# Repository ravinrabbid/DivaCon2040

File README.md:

# DivaCon2040 - Firmware for RP2040/RP2350 based Project Diva controllers

DivaCon2040 is a firmware for DIY Project Diva Arcade controllers based on the RP2040/RP2350 microcontroller as found on the Raspberry Pi Pico.

It is pretty much tailored to this specific use case, if you are looking for something universal, ready-to-flash and on-the-fly configurable I'd recommend to have a look at more generic approaches like [GP2040-CE](https://github.com/OpenStickCommunity/GP2040-CE). If you however want build something more specialized or custom, feel free to use this project as a base, it is designed to be somewhat modular and should be easy remodel. See [DonCon2040](https://github.com/ravinrabbid/DonCon2040) for an example on how this could look like.

If you have any questions about the project in general or need hints how to build this thing, feel free to open a [discussion](https://github.com/ravinrabbid/DivaCon2040/discussions) anytime!

## Features

- Various controller emulation modes
  - HORI PS4-161 Project Diva Arcade Controller
  - HORI NSW-230 Project Diva Arcade Controller
  - PD-Loader Arcade Controller (Compatible with [PD-Loader](https://github.com/PDModdingCommunity/PD-Loader/)'s Divaller driver)
  - PS4 Compatibility (will work on PS4, see [PS4 Authentication](#ps4-authentication) for details)
  - Dualshock 4 (Will be recognised as DS4 on PC/Steam, but does not work on an actual PS4!)
  - Dualshock 3
  - Switch Pro Controller
  - XInput
  - Keyboard
  - MIDI
  - Debug mode (will output current state via USB serial and allow direct flashing)
- Arcade Style Touch Slider for arcade controller emulation modes (In Project Diva Games with arcade controller support: Enter the 'Customize' menu from song selection and enable arcade controller support under 'Game/Control Config' -> 'Arcade Controller Settings' for the slider to work properly.)
- Slider to analog stick mapping for standard controller modes
- Option to mirror face buttons to directional pad for games with 'W'-arrows
- 1000Hz Polling Rate, ~2.4ms average latency, <0.7ms Jitter (Tested with [Gamepadla](https://github.com/cakama3a/Gamepadla)/[GPDL](https://github.com/cakama3a/GPDL/))
- Slider illumination using WS2812 LED strip (can be controlled by PD-Loader)
- Button illumination (can be controlled by PD-Loader)
- Basic configuration via on-screen menu on attached OLED screen
- BPM counter

## Game Compatibility

| Title                                                                       | Platform | Official Arcade Slider Support |      Recommended Mode      | Notes                                                                                                                                                                                                                                                                                                                                                |
| --------------------------------------------------------------------------- | :------: | :----------------------------: | :------------------------: | :--------------------------------------------------------------------------------------------------------------------------------------------------------------------------------------------------------------------------------------------------------------------------------------------------------------------------------------------------- |
| Hatsune Miku -Project DIVA- Dreamy Theater                                  |   PS3    |               No               | Dualshock 3 + 'Double Btn' | - **Untested** but will likely work.<br>- Slider can be used for Star notes.<br>- Enable 'Double Btn' to make hitting 'W'-arrows easier.                                                                                                                                                                                                             |
| Hatsune Miku -Project DIVA- Dreamy Theater 2nd                              |   PS3    |               No               | Dualshock 3 + 'Double Btn' | - Slider can be used for Star notes.<br>- Enable 'Double Btn' to make hitting 'W'-arrows easier.                                                                                                                                                                                                                                                     |
| Hatsune Miku -Project DIVA- Dreamy Theater extend                           |   PS3    |               No               | Dualshock 3 + 'Double Btn' | - **Untested** but will likely work.<br>- Slider can be used for Star notes.<br>- Enable 'Double Btn' to make hitting 'W'-arrows easier.                                                                                                                                                                                                             |
| Hatsune Miku -Project DIVA- F                                               |   PS3    |               No               | Dualshock 3 + 'Double Btn' | - Slider can be used for Star notes.<br>- Enable 'Double Btn' to make hitting 'W'-arrows easier.                                                                                                                                                                                                                                                     |
| Hatsune Miku -Project DIVA- F2nd                                            |   PS3    |               No               | Dualshock 3 + 'Double Btn' | - Slider can be used for Star notes.<br>- Enable 'Double Btn' to make hitting 'W'-arrows easier.                                                                                                                                                                                                                                                     |
| Hatsune Miku -Project DIVA- Future Tone                                     |   PS4    |               No               |         PS4 Compat         | - See [PS4 Authentication](#ps4-authentication)<br>- Game does not support arcade style slider, stick emulation will be used.                                                                                                                                                                                                                        |
| Hatsune Miku -Project DIVA- Future Tone DX                                  |   PS4    |              Yes               |          PS4 Diva          | - See [PS4 Authentication](#ps4-authentication)<br>- From song selection enter the 'Customize' menu and enable arcade controller support under 'Game/Control Config' -> 'Arcade Controller Settings'.                                                                                                                                                |
| Hatsune Miku -Project DIVA- X                                               |   PS4    |               No               | PS4 Compat + 'Double Btn'  | - See [PS4 Authentication](#ps4-authentication)<br>- Slider can be used for Star notes.<br>- Enable 'Double Btn' to make hitting 'W'-arrows easier.                                                                                                                                                                                                  |
| Hatsune Miku: Project DIVA Mega Mix / Hatsune Miku -Project DIVA- MEGA39’s  |  Switch  |              Yes               |        Switch Diva         | - When starting the game, choose 'Arcade Mode'.<br> - From song selection enter the 'Customize' menu and enable arcade controller support under 'Game/Control Config' -> 'Arcade Controller Settings'.                                                                                                                                               |
| Hatsune Miku -Project DIVA- Arcade Future Tone (PDLoader)                   |    PC    |              Yes               |         PDL Arcade         | - Should work out-of-the-box. (You might need to enable `slider_in_menus` in `keyconfig.ini` and `Hardware_Slider` in `config.ini`).<br>- 'PS4 Diva' also works, see [here](https://github.com/PDModdingCommunity/PD-Loader/wiki/3%29-Usage,-Modules-%28Costumes%29,-Troubleshooting#official-hori-ps4-ft-controller-with-slider) for configuration. |
| Hatsune Miku: Project DIVA Mega 39s+ / Hatsune Miku: Project DIVA Mega Mix+ |    PC    |              Yes               |  PS4 Diva or Switch Diva   | - From song selection enter the 'Customize' menu and enable arcade controller support under 'Game/Control Config' -> 'Arcade Controller Settings'.                                                                                                                                                                                                   |

## Building

I highly recommend to build the firmware yourself so you can make adjustments in `include/GlobalConfiguration.h` to match your specific controller build.
If you still want to use a [binary release](https://github.com/ravinrabbid/DivaCon2040/releases), you need to connect everything according the default configuration as described [here](SCHEMATIC.md).

### VSCode (Windows, Linux, MacOS)

Install [VSCode](https://code.visualstudio.com/) and get the [Raspberry Pi Pico](https://marketplace.visualstudio.com/items?itemName=raspberry-pi.raspberry-pi-pico) extension. From the extension choose 'Import Project' and select the folder where you've checked out this repository, then use 'Compile Project'.

### CLI

See [pico-sdk readme](https://github.com/raspberrypi/pico-sdk/blob/master/README.md#quick-start-your-own-project) for a list of pre-requisites.

Use the environment variables `PICO_SDK_PATH` to use a local pico-sdk, and `PICO_BOARD` to select another target board.
By default the pico-sdk will be fetched from Github and the target board will be "pico".

For Rasberry Pi Pico:

```sh
cmake -B build -DPICO_BOARD="pico"
cmake --build build
```

For Rasberry Pi Pico 2:

```sh
cmake -B build -DPICO_BOARD="pico2"
cmake --build build
```

## Configuration

Options which you probably want to change more regularly can be changed using the on-screen menu on the attached OLED display, hold both Start and Select for 2 seconds to enter it:

- Controller emulation mode
- Touch Slider LED mode, color and brightness
- Face button to directional pad mirroring
- Reset settings to defaults
- Enter BOOTSEL mode for firmware flashing

Those settings are persisted to flash memory if you choose 'Save' when exiting the Menu and will survive power cycles.

Everything else is compiled statically into the firmware. You can find defaults and hardware configuration in `include/GlobalConfiguration.h`. This covers default controller emulation mode, button pins, i2c pins, addresses and speed and slider type.

### PS4 Authentication

The PS4 needs a controller to sign a cryptographic challenge every few seconds, otherwise it will stop working after around 8 minutes after plugging in. For the Project Diva games this is somewhat bearable, since you can re-plug the controller before starting each song to avoid running into the timeout during gameplay. Still, this is annoying.

DivaCon2040 can sign those challenges, but you will need to obtain some data from an original DS4 and compile it into the firmware. You will need a serial, signature and private key file. I can't and won't help you how to obtain those, you'll need to figure this out yourself.

To build the firmware run `scripts/generateAuthConfig.py` in the folder where you placed the required files. Copy the resulting `PS4AuthConfiguration.h` to the `include` directory, replacing the existing header. Then build the firmware as described in [Building](#building).

Signing the challenge will block the second core of the RP2040 for 2-3 seconds, so LED animations and the display will appear stuck from time to time. Input handling is unaffected.
On the RP2350 SHA256 is hardware accelerated, so signing time is reduced to about 1 second.

## Hardware

### Main IO Board

This project was designed and tested on the Raspberry Pi Pico. Other RP2040/RP2350 boards should also work if they expose enough GPIOs.

You can find the [DivaConIO board](pcb/DivaConIO) in the *pcb* subfolder. This conveniently breaks out the GPIO pins into connectors and already comes with drivers for the button LEDs and level shifting for the slider LEDs.

It is however perfectly possible to build this on a piece of stripboard or the like. [See this schematic here](SCHEMATIC.md) for details.

### Touch Slider

The touch slider resembles the the slider of Project Diva Arcade Controllers and Cabinets, being a row of 32 individual touch sensors. For the two arcade controller emulation modes, the 32 sensors are mapped to the analog stick axes as described [here](https://gist.github.com/dogtopus/48ad10409aa4ad5c408e31287623e167) and work just like the original controllers in-game. In Project Diva games which support arcade controllers (i.e. Mega Mix on PC/Switch), enter the 'Customize' menu from song selection and enable arcade controller support under 'Game/Control Config' -> 'Arcade Controller Settings' for the slider to work properly.

For other controller emulation modes, swipes on the left half of the slider will move the left stick left and right, while swipes on the right half will do the same on the right stick.

#### Electronics

The current Touch Slider is based on the MPR121 Capacitive Touch Sensor Controller. While the MPR121 seems to have a somewhat bad reputation to be hard to work with, I've had no issues with it so far and it works near flawlessly. That main downside is that is is out-of-production, there is however still sufficient supply on the usual marketplaces.

Current alternatives like the CAP1188 are almost universally to slow. During a quick slide, a finger spends roughly 10ms on a single touch pad while most controllers need scan cycles of at least 16-35ms. The MPR121 on the contrary can be configured down to around 1ms. The Lumissil IS31SE5117A looks promising, but I couldn't get it to work yet. Other than that microcontrollers with integrated touch controllers are an option, but I don't want to go down that route since there already is the [LKP](https://github.com/Project-Alpaca/LKP) which does this. The LKP seems to have an i2c slave mode, so if you have access to one feel free to get in touch. I'd be happy to work on supporting the LKP but need someone to test.

All MPR121 controllers are attached to the same i2c bus, so make sure to have them use different i2c addresses accordingly. There is a slider variant with three and one with four controllers which can be configured in `include/GlobalConfiguration.h` (The four controller variant is the default). See below tables for the electrode mapping:

##### Three MPR121

|               | **MPR 0** | **MPR 1** | **MPR 2** |
| ------------- | :-------: | :-------: | :-------: |
| **Pin**       |   0..11   |   2..9    |   0..11   |
| **Electrode** |  31..20   |  19..12   |   11..0   |

##### Four MPR121

|               | **MPR 0** | **MPR 1** | **MPR 2** | **MPR 3** |
| ------------- | :-------: | :-------: | :-------: | :-------: |
| **Pin**       |   4..11   |   4..11   |   4..11   |   4..11   |
| **Electrode** |  31..24   |  13..16   |   15..8   |   7..0    |

The MPR121s are setup for auto configuration with parameters taken from the [Adafruit MPR121 Arduino Library](https://github.com/adafruit/Adafruit_MPR121). The 'FDL falling' value has been tweaked to allow slow slides. You might want to adjust the touch and release thresholds to your specific build.

#### Construction

There are two variants which both work equivalently well in my experience: You can use the [DivaConSlider board](pcb/DivaConSliderMpr) from the *pcb* subfolder which hosts the MPR121s, electrodes and LEDs or you can build it by hand without a pcb.

For the latter I had success using 15mm wide copper tape strips with 2mm spacing in-between, aligning them properly using a 3D printed jig. Those are attached to off-the-shelf MPR121 breakout boards using the thinnest wire possible to reduce parasitic capacitance.

Both variants are covered by a sandwich made out of some thin 3M 468MP or 467MP adhesive, paper for the artwork, another layer of adhesive and 3mm of frosted acrylic. Is seems to be pretty essential to use the proper adhesive here to get an even bond and to avoid any air between the layers. The 3M tape mentioned above is recommended in the MPR121 application notes. I can be a bit hard to work with, but is manageable by spraying some soapy water on the surface beforehand to ease alignment.

For illumination of the non-pcb variant, I used [Adafruit Side Light NeoPixel LED PCB Bars](https://www.adafruit.com/product/3729) which have the perfect hight and spacing to light up each segment with two LEDs each, but other WS2812 compatible strips should work as well.

One word on the slider dimensions: Those are not arcade accurate but slightly larger. This stems from constraints of me building the non-pcb variant first (i.e. available copper tape and LED strip dimensions). See [here](https://projectdiva.net/community/threads/i-bought-a-project-diva-arcade-future-tone-cabinet.2307/page-3#post-18087) for the actual dimensions or have a look at the [LKP](https://github.com/Project-Alpaca/LKP).

### Buttons

Buttons are hooked up directly to the GPIO pins, pulling the pin to ground when pressed.

Supported are:

- Four face buttons, which are mapped according to the cardinal directions they appear on the respective controllers (North/East/South/West)
- DPad/Hat (Up/Down/Left/Right)
- Two shoulder buttons for each side (L1/L2/R1/R2)
- Two Stick buttons (L3/R3)
- Three vendor specific buttons (Options/TouchPad/PS on DS4, Start/Select/PS on DS3, +/-/Home on Switch, Start/Back/Guide on XInput)

For the four big buttons I used generic 100mm "Massive Arcade Button"s since those are much cheaper than the original Sanwa OBSA-100UMQ.
They have same size an can be easily improved with the original OBSA-SP-200 200g springs and better switches, like the ridiculously expensive Sanwa OBSA-LHSXF or [steelpuxnastik's excellent DIY switches](https://github.com/steelpuxnastik/SHINSANWASWITCH) for a more authentic feel.

The other buttons are cheap generic 24mm arcade buttons.

### Button LEDs

Illumination for the four face buttons can be controlled by GPIO pins. I recommend to not directly hook up the LEDs to the GPIO pins, but rather use a simple transistor based driving circuit since the power than can be delivered through the GPIOs is rather limited.

### OLED Display

Just a standard SSD1306 OLED display with 128x64 resolution hooked up to the second i2c bus. Mind that the display is mandatory for changing any settings directly on the controller, if you want to omit it, change the defaults within the code accordingly (or navigate the menu blindly).

### The 'Box'

The enclosure is build with lasercut 5mm opaque black acrylic panels held together by aluminum profiles and some 3D printed spacers.
Edges and the cradles the touch slider sits in are also 3D printed. The Artwork is sandwiched behind an additional layer of 4mm transparent acrylic.

## Acknowledgements

- Adafruit for the figuring out some working [MPR121 settings](https://github.com/adafruit/Adafruit_MPR121)
- [daschr](https://github.com/daschr) for the [SSD1306 OLED driver](https://github.com/daschr/pico-ssd1306)
- [FeralAI](https://github.com/FeralAI) for the inspiration and Dualshock3/XInput driver from the [GP2040 Project](https://github.com/FeralAI/GP2040)
- [dogtopus](https://github.com/dogtopus) for his research on the arcade slider and various contributions to many controller related projects
- [steelpuxnastik](https://github.com/steelpuxnastik) for the excellent [SHINSANWASWITCH](https://github.com/steelpuxnastik/SHINSANWASWITCH)
- The linux kernel contributors for documenting the game controllers in their drivers

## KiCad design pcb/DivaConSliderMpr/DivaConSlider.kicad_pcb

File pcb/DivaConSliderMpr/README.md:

# DivaConSlider - Mpr121 based touch slider for the DivaCon2040

This board hosts four MPR121 capacitive touch controllers along with the slider electrodes and LEDs for illumination.

## Notes

- The Display module can be installed optionally.
- Dimensions are not arcade accurate.

## Bill of Materials

| **Reference**              |             **Description**              |     **Digikey Part**      |                                  **Notes**                                   |
| -------------------------- | :--------------------------------------: | :-----------------------: | :--------------------------------------------------------------------------: |
| U1-U4                      |        MPR121QR2 Touch Controller        |           n.a.            |    Discontinued, still available on marketplaces like eBay or AliExpress.    |
| D1-D64                     |           SK6812B SIDE RGB LED           |       1528-4691-ND        |                                                                              |
| C1-C72                     |       0.1µF SMD Ceramic Capacitor        |      1276-1003-1-ND       |                                                                              |
| R1,R3,R5,R7,R9,R10,R11,R12 |            10kΩ SMD Resistor             | 2019-RK73H2ATTD1002FTR-ND | R11 and R12 are only needed if the Display module does not have i2c pull-ups |
| R2,R4,R6,R8                |            75kΩ SMD Resistor             | 2019-RK73H2ATTD7502FTR-ND |                                                                              |
| R13                        |            470Ω SMD Resistor             | 2019-RK73H2ATTD4700FTR-ND |                                                                              |
| J1,J2,J3                   |     SWH201 Vertical 4 Pin Header 2mm     |         S9457-ND          |                 S9406-ND plus S9475CT-ND is the counterpart                  |
| J4                         | 0.96" SSD1306 128x64 OLED Display module | 3190-DLC0096DNOG-W-10-ND  |                                   optional                                   |

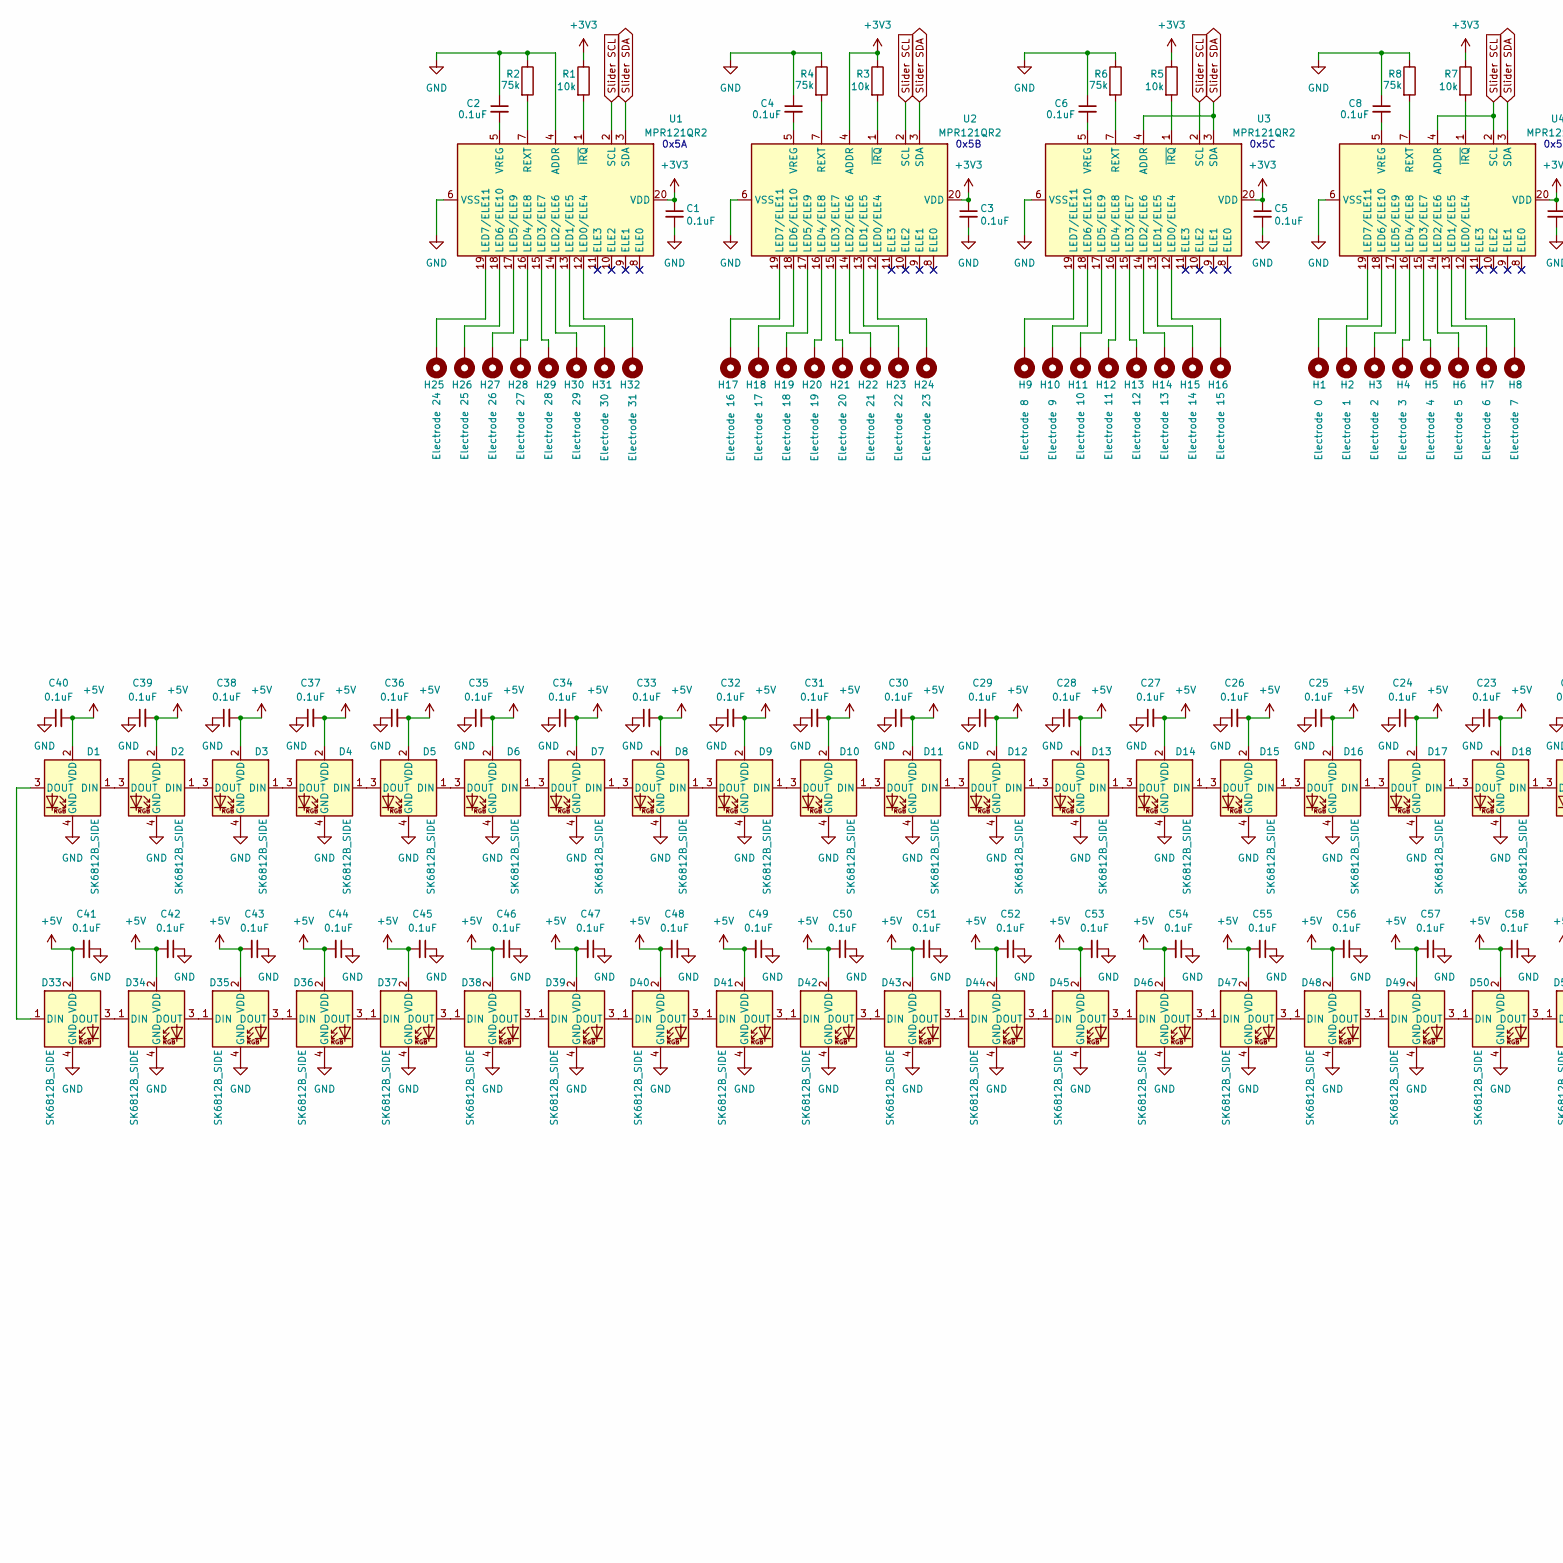
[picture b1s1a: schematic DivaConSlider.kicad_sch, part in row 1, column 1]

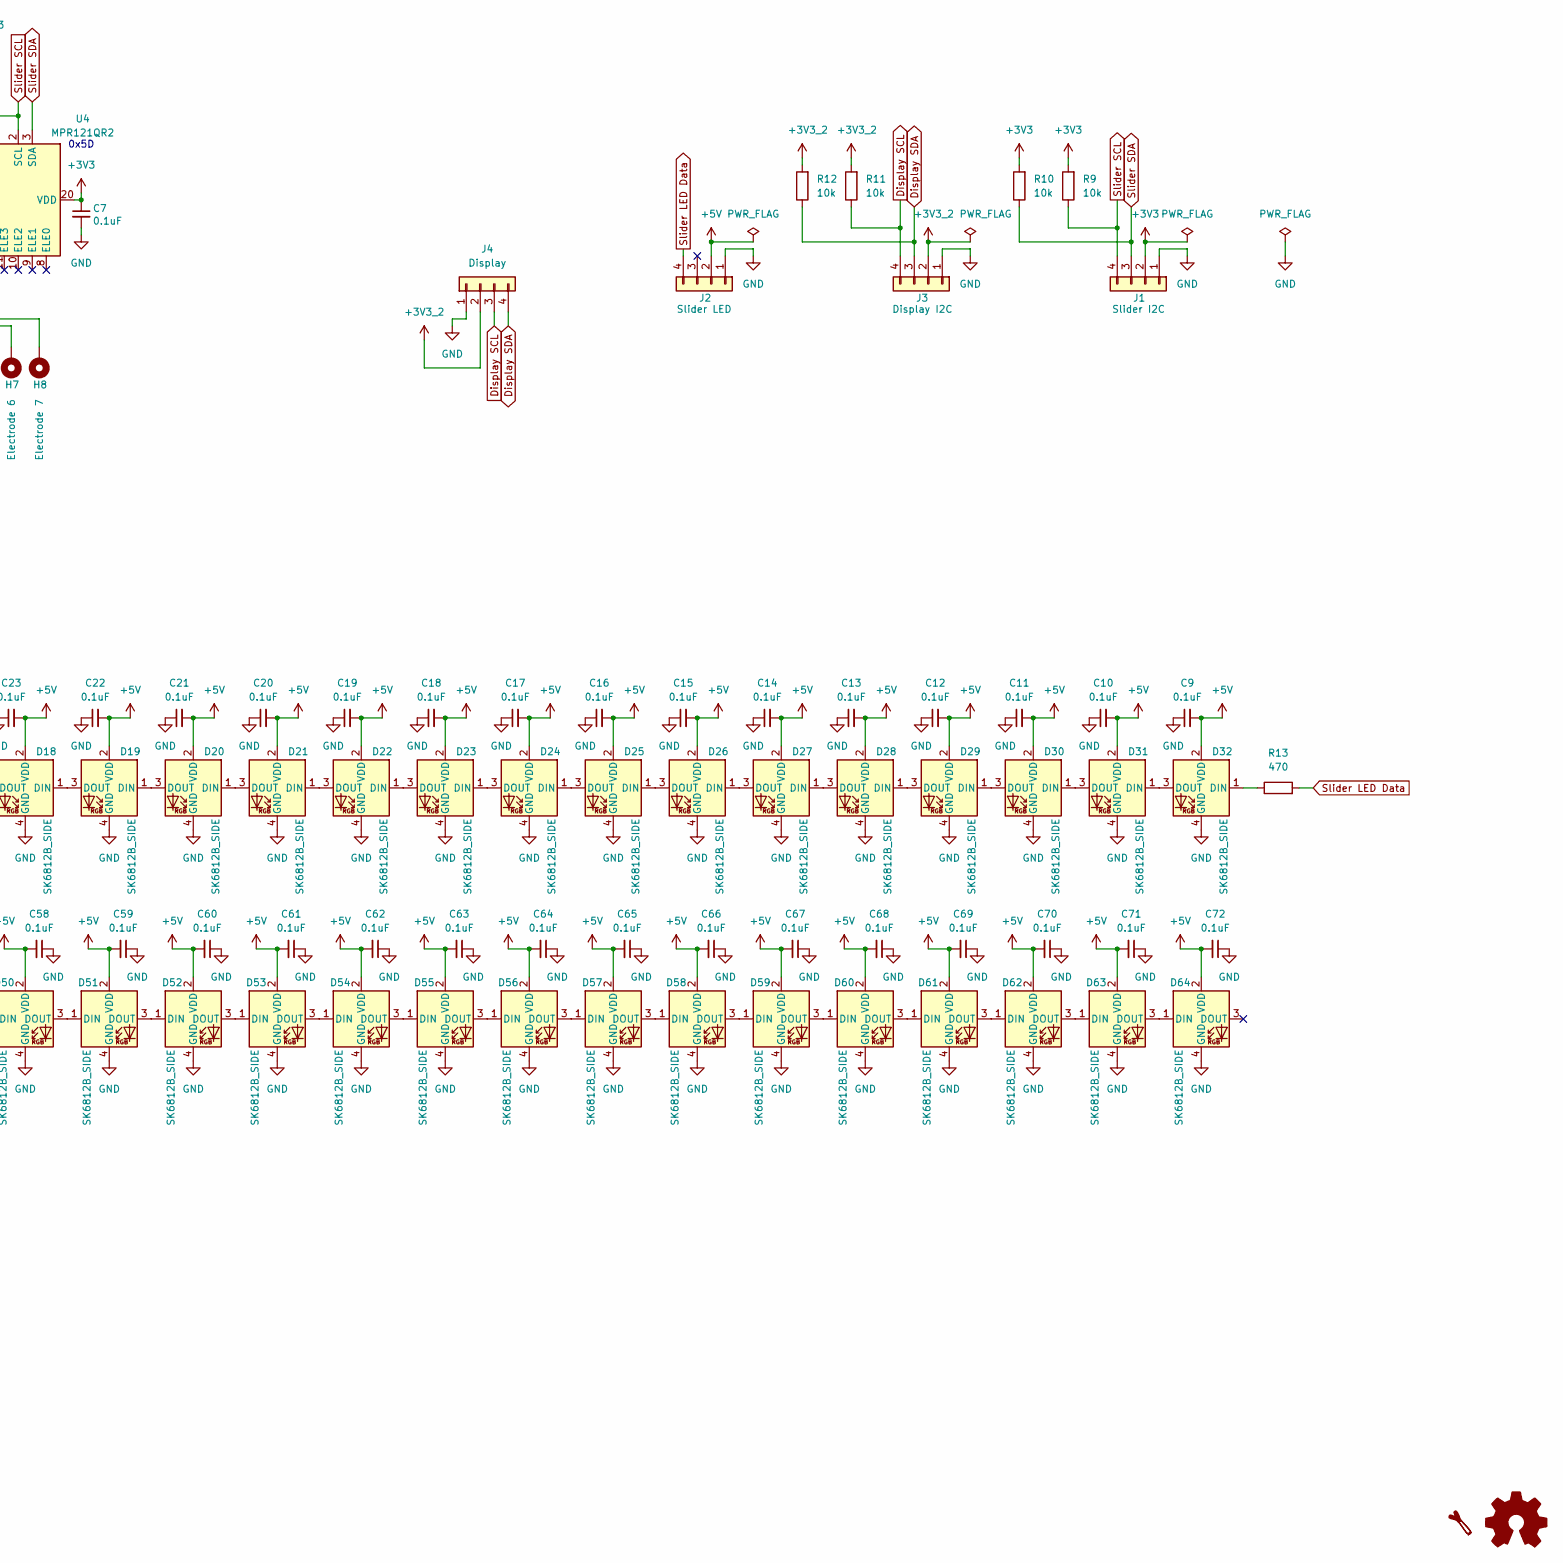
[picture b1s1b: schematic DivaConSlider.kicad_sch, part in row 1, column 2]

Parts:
C1, C2, C3, C4, C5, C6, C7, C8, C9, C10, C11, C12, C13, C14, C15, C16, C17, C18, C19, C20, C21, C22, C23, C24, C25, C26, C27, C28, C29, C30, C31, C32, C33, C34, C35, C36, C37, C38, C39, C40, C41, C42, C43, C44, C45, C46, C47, C48, C49, C50, C51, C52, C53, C54, C55, C56, C57, C58, C59, C60, C61, C62, C63, C64, C65, C66, C67, C68, C69, C70, C71, C72: 0.1uF; C_0805_2012Metric_Pad1.18x1.45mm_HandSolder
D1, D2, D3, D4, D5, D6, D7, D8, D9, D10, D11, D12, D13, D14, D15, D16, D17, D18, D19, D20, D21, D22, D23, D24, D25, D26, D27, D28, D29, D30, D31, D32, D33, D34, D35, D36, D37, D38, D39, D40, D41, D42, D43, D44, D45, D46, D47, D48, D49, D50, D51, D52, D53, D54, D55, D56, D57, D58, D59, D60, D61, D62, D63, D64: SK6812B_SIDE; LED_SK6812B_SIDE
H1: Electrode 0; Touchpad_15mmx42mm
H2: Electrode 1; Touchpad_15mmx42mm
H3: Electrode 2; Touchpad_15mmx42mm
H4: Electrode 3; Touchpad_15mmx42mm
H5: Electrode 4; Touchpad_15mmx42mm
H6: Electrode 5; Touchpad_15mmx42mm
H7: Electrode 6; Touchpad_15mmx42mm
H8: Electrode 7; Touchpad_15mmx42mm
H9: Electrode 8; Touchpad_15mmx42mm
H10: Electrode 9; Touchpad_15mmx42mm
H11: Electrode 10; Touchpad_15mmx42mm
H12: Electrode 11; Touchpad_15mmx42mm
H13: Electrode 12; Touchpad_15mmx42mm
H14: Electrode 13; Touchpad_15mmx42mm
H15: Electrode 14; Touchpad_15mmx42mm
H16: Electrode 15; Touchpad_15mmx42mm
H17: Electrode 16; Touchpad_15mmx42mm
H18: Electrode 17; Touchpad_15mmx42mm
H19: Electrode 18; Touchpad_15mmx42mm
H20: Electrode 19; Touchpad_15mmx42mm
H21: Electrode 20; Touchpad_15mmx42mm
H22: Electrode 21; Touchpad_15mmx42mm
H23: Electrode 22; Touchpad_15mmx42mm
H24: Electrode 23; Touchpad_15mmx42mm
H25: Electrode 24; Touchpad_15mmx42mm
H26: Electrode 25; Touchpad_15mmx42mm
H27: Electrode 26; Touchpad_15mmx42mm
H28: Electrode 27; Touchpad_15mmx42mm
H29: Electrode 28; Touchpad_15mmx42mm
H30: Electrode 29; Touchpad_15mmx42mm
H31: Electrode 30; Touchpad_15mmx42mm
H32: Electrode 31; Touchpad_15mmx42mm
J1: Slider I2C; JST_PH_B4B-PH-K_1x04_P2.00mm_Vertical
J2: Slider LED; JST_PH_B4B-PH-K_1x04_P2.00mm_Vertical
J3: Display I2C; JST_PH_B4B-PH-K_1x04_P2.00mm_Vertical
J4: Display; PinHeader_1x04_P2.54mm_Vertical
R1, R3, R5, R7, R9, R10, R11, R12: 10k; R_0805_2012Metric_Pad1.20x1.40mm_HandSolder
R2, R4, R6, R8: 75k; R_0805_2012Metric_Pad1.20x1.40mm_HandSolder
R13: 470; R_0805_2012Metric_Pad1.20x1.40mm_HandSolder
U1, U2, U3, U4: MPR121QR2; UQFN-20_3x3mm_P0.4mm

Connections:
+3V3: C1.1, C3.1, C5.1, C7.1, J1.2, R1.1, R3.1, R5.1, R7.1, R9.2, R10.2, U1.20 (VDD), U2.4 (ADDR), U2.20 (VDD), U3.20 (VDD), U4.20 (VDD)
+3V3_2: J3.2, J4.2, R11.2, R12.2
+5V: C9.2, C10.2, C11.2, C12.2, C13.2, C14.2, C15.2, C16.2, C17.2, C18.2, C19.2, C20.2, C21.2, C22.2, C23.2, C24.2, C25.2, C26.2, C27.2, C28.2, C29.2, C30.2, C31.2, C32.2, C33.2, C34.2, C35.2, C36.2, C37.2, C38.2, C39.2, C40.2, C41.2, C42.2, C43.2, C44.2, C45.2, C46.2, C47.2, C48.2, C49.2, C50.2, C51.2, C52.2, C53.2, C54.2, C55.2, C56.2, C57.2, C58.2, C59.2, C60.2, C61.2, C62.2, C63.2, C64.2, C65.2, C66.2, C67.2, C68.2, C69.2, C70.2, C71.2, C72.2, D1.2 (VDD), D2.2 (VDD), D3.2 (VDD), D4.2 (VDD), D5.2 (VDD), D6.2 (VDD), D7.2 (VDD), D8.2 (VDD), D9.2 (VDD), D10.2 (VDD), D11.2 (VDD), D12.2 (VDD), D13.2 (VDD), D14.2 (VDD), D15.2 (VDD), D16.2 (VDD), D17.2 (VDD), D18.2 (VDD), D19.2 (VDD), D20.2 (VDD), D21.2 (VDD), D22.2 (VDD), D23.2 (VDD), D24.2 (VDD), D25.2 (VDD), D26.2 (VDD), D27.2 (VDD), D28.2 (VDD), D29.2 (VDD), D30.2 (VDD), D31.2 (VDD), D32.2 (VDD), D33.2 (VDD), D34.2 (VDD), D35.2 (VDD), D36.2 (VDD), D37.2 (VDD), D38.2 (VDD), D39.2 (VDD), D40.2 (VDD), D41.2 (VDD), D42.2 (VDD), D43.2 (VDD), D44.2 (VDD), D45.2 (VDD), D46.2 (VDD), D47.2 (VDD), D48.2 (VDD), D49.2 (VDD), D50.2 (VDD), D51.2 (VDD), D52.2 (VDD), D53.2 (VDD), D54.2 (VDD), D55.2 (VDD), D56.2 (VDD), D57.2 (VDD), D58.2 (VDD), D59.2 (VDD), D60.2 (VDD), D61.2 (VDD), D62.2 (VDD), D63.2 (VDD), D64.2 (VDD), J2.2
Display SCL: J3.4, J4.3, R11.1
Display SDA: J3.3, J4.4, R12.1
GND: C1.2, C2.1, C3.2, C4.1, C5.2, C6.1, C7.2, C8.1, C9.1, C10.1, C11.1, C12.1, C13.1, C14.1, C15.1, C16.1, C17.1, C18.1, C19.1, C20.1, C21.1, C22.1, C23.1, C24.1, C25.1, C26.1, C27.1, C28.1, C29.1, C30.1, C31.1, C32.1, C33.1, C34.1, C35.1, C36.1, C37.1, C38.1, C39.1, C40.1, C41.1, C42.1, C43.1, C44.1, C45.1, C46.1, C47.1, C48.1, C49.1, C50.1, C51.1, C52.1, C53.1, C54.1, C55.1, C56.1, C57.1, C58.1, C59.1, C60.1, C61.1, C62.1, C63.1, C64.1, C65.1, C66.1, C67.1, C68.1, C69.1, C70.1, C71.1, C72.1, D1.4 (GND), D2.4 (GND), D3.4 (GND), D4.4 (GND), D5.4 (GND), D6.4 (GND), D7.4 (GND), D8.4 (GND), D9.4 (GND), D10.4 (GND), D11.4 (GND), D12.4 (GND), D13.4 (GND), D14.4 (GND), D15.4 (GND), D16.4 (GND), D17.4 (GND), D18.4 (GND), D19.4 (GND), D20.4 (GND), D21.4 (GND), D22.4 (GND), D23.4 (GND), D24.4 (GND), D25.4 (GND), D26.4 (GND), D27.4 (GND), D28.4 (GND), D29.4 (GND), D30.4 (GND), D31.4 (GND), D32.4 (GND), D33.4 (GND), D34.4 (GND), D35.4 (GND), D36.4 (GND), D37.4 (GND), D38.4 (GND), D39.4 (GND), D40.4 (GND), D41.4 (GND), D42.4 (GND), D43.4 (GND), D44.4 (GND), D45.4 (GND), D46.4 (GND), D47.4 (GND), D48.4 (GND), D49.4 (GND), D50.4 (GND), D51.4 (GND), D52.4 (GND), D53.4 (GND), D54.4 (GND), D55.4 (GND), D56.4 (GND), D57.4 (GND), D58.4 (GND), D59.4 (GND), D60.4 (GND), D61.4 (GND), D62.4 (GND), D63.4 (GND), D64.4 (GND), J1.1, J2.1, J3.1, J4.1, R2.1, R4.1, R6.1, R8.1, U1.4 (ADDR), U1.6 (VSS), U2.6 (VSS), U3.6 (VSS), U4.6 (VSS)
unnamed: D1.1 (DIN), D2.3 (DOUT)
unnamed: D1.3 (DOUT), D33.1 (DIN)
unnamed: D2.1 (DIN), D3.3 (DOUT)
unnamed: D3.1 (DIN), D4.3 (DOUT)
unnamed: D4.1 (DIN), D5.3 (DOUT)
unnamed: D5.1 (DIN), D6.3 (DOUT)
unnamed: D6.1 (DIN), D7.3 (DOUT)
unnamed: D7.1 (DIN), D8.3 (DOUT)
unnamed: D8.1 (DIN), D9.3 (DOUT)
unnamed: D10.1 (DIN), D11.3 (DOUT)
unnamed: D9.1 (DIN), D10.3 (DOUT)
unnamed: D11.1 (DIN), D12.3 (DOUT)
unnamed: D12.1 (DIN), D13.3 (DOUT)
unnamed: D13.1 (DIN), D14.3 (DOUT)
unnamed: D14.1 (DIN), D15.3 (DOUT)
unnamed: D15.1 (DIN), D16.3 (DOUT)
unnamed: D16.1 (DIN), D17.3 (DOUT)
unnamed: D17.1 (DIN), D18.3 (DOUT)
unnamed: D18.1 (DIN), D19.3 (DOUT)
unnamed: D19.1 (DIN), D20.3 (DOUT)
unnamed: D20.1 (DIN), D21.3 (DOUT)
unnamed: D21.1 (DIN), D22.3 (DOUT)
unnamed: D22.1 (DIN), D23.3 (DOUT)
unnamed: D23.1 (DIN), D24.3 (DOUT)
unnamed: D24.1 (DIN), D25.3 (DOUT)
unnamed: D25.1 (DIN), D26.3 (DOUT)
unnamed: D26.1 (DIN), D27.3 (DOUT)
unnamed: D27.1 (DIN), D28.3 (DOUT)
unnamed: D28.1 (DIN), D29.3 (DOUT)
unnamed: D29.1 (DIN), D30.3 (DOUT)
unnamed: D30.1 (DIN), D31.3 (DOUT)
unnamed: D31.1 (DIN), D32.3 (DOUT)
unnamed: D32.1 (DIN), R13.1
unnamed: D33.3 (DOUT), D34.1 (DIN)
unnamed: D34.3 (DOUT), D35.1 (DIN)
unnamed: D35.3 (DOUT), D36.1 (DIN)
unnamed: D36.3 (DOUT), D37.1 (DIN)
unnamed: D37.3 (DOUT), D38.1 (DIN)
unnamed: D38.3 (DOUT), D39.1 (DIN)
unnamed: D39.3 (DOUT), D40.1 (DIN)
unnamed: D40.3 (DOUT), D41.1 (DIN)
unnamed: D41.3 (DOUT), D42.1 (DIN)
unnamed: D42.3 (DOUT), D43.1 (DIN)
unnamed: D43.3 (DOUT), D44.1 (DIN)
unnamed: D44.3 (DOUT), D45.1 (DIN)
unnamed: D45.3 (DOUT), D46.1 (DIN)
unnamed: D46.3 (DOUT), D47.1 (DIN)
unnamed: D47.3 (DOUT), D48.1 (DIN)
unnamed: D48.3 (DOUT), D49.1 (DIN)
unnamed: D49.3 (DOUT), D50.1 (DIN)
unnamed: D50.3 (DOUT), D51.1 (DIN)
unnamed: D51.3 (DOUT), D52.1 (DIN)
unnamed: D52.3 (DOUT), D53.1 (DIN)
unnamed: D53.3 (DOUT), D54.1 (DIN)
unnamed: D54.3 (DOUT), D55.1 (DIN)
unnamed: D55.3 (DOUT), D56.1 (DIN)
unnamed: D56.3 (DOUT), D57.1 (DIN)
unnamed: D57.3 (DOUT), D58.1 (DIN)
unnamed: D58.3 (DOUT), D59.1 (DIN)
unnamed: D59.3 (DOUT), D60.1 (DIN)
unnamed: D60.3 (DOUT), D61.1 (DIN)
unnamed: D61.3 (DOUT), D62.1 (DIN)
unnamed: D62.3 (DOUT), D63.1 (DIN)
unnamed: D63.3 (DOUT), D64.1 (DIN)
unnamed: H32.1, U1.12 (LED0/ELE4)
unnamed: H31.1, U1.13 (LED1/ELE5)
unnamed: H30.1, U1.14 (LED2/ELE6)
unnamed: H29.1, U1.15 (LED3/ELE7)
unnamed: H28.1, U1.16 (LED4/ELE8)
unnamed: H27.1, U1.17 (LED5/ELE9)
unnamed: H26.1, U1.18 (LED6/ELE10)
unnamed: H25.1, U1.19 (LED7/ELE11)
unnamed: R2.2, U1.7 (REXT)
unnamed: C2.2, U1.5 (VREG)
unnamed: R1.2, U1.1 (~IRQ)
unnamed: H24.1, U2.12 (LED0/ELE4)
unnamed: H23.1, U2.13 (LED1/ELE5)
unnamed: H22.1, U2.14 (LED2/ELE6)
unnamed: H21.1, U2.15 (LED3/ELE7)
unnamed: H20.1, U2.16 (LED4/ELE8)
unnamed: H19.1, U2.17 (LED5/ELE9)
unnamed: H18.1, U2.18 (LED6/ELE10)
unnamed: H17.1, U2.19 (LED7/ELE11)
unnamed: R4.2, U2.7 (REXT)
unnamed: C4.2, U2.5 (VREG)
unnamed: R3.2, U2.1 (~IRQ)
unnamed: H16.1, U3.12 (LED0/ELE4)
unnamed: H15.1, U3.13 (LED1/ELE5)
unnamed: H14.1, U3.14 (LED2/ELE6)
unnamed: H13.1, U3.15 (LED3/ELE7)
unnamed: H12.1, U3.16 (LED4/ELE8)
unnamed: H11.1, U3.17 (LED5/ELE9)
unnamed: H10.1, U3.18 (LED6/ELE10)
unnamed: H9.1, U3.19 (LED7/ELE11)
unnamed: R6.2, U3.7 (REXT)
unnamed: C6.2, U3.5 (VREG)
unnamed: R5.2, U3.1 (~IRQ)
unnamed: H8.1, U4.12 (LED0/ELE4)
unnamed: H7.1, U4.13 (LED1/ELE5)
unnamed: H6.1, U4.14 (LED2/ELE6)
unnamed: H5.1, U4.15 (LED3/ELE7)
unnamed: H4.1, U4.16 (LED4/ELE8)
unnamed: H3.1, U4.17 (LED5/ELE9)
unnamed: H2.1, U4.18 (LED6/ELE10)
unnamed: H1.1, U4.19 (LED7/ELE11)
unnamed: R8.2, U4.7 (REXT)
unnamed: C8.2, U4.5 (VREG)
unnamed: R7.2, U4.1 (~IRQ)
Slider LED Data: J2.4, R13.2
Slider SCL: J1.4, R9.1, U1.2 (SCL), U2.2 (SCL), U3.2 (SCL), U4.2 (SCL), U4.4 (ADDR)
Slider SDA: J1.3, R10.1, U1.3 (SDA), U2.3 (SDA), U3.3 (SDA), U3.4 (ADDR), U4.3 (SDA)

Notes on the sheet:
0x5B
0x5A
0x5D
0x5C

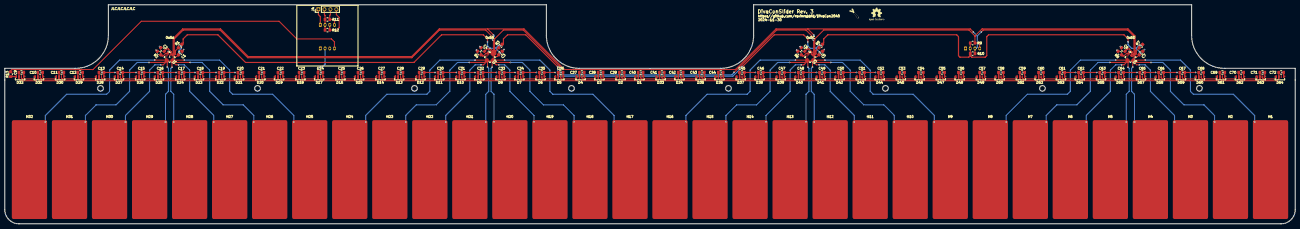
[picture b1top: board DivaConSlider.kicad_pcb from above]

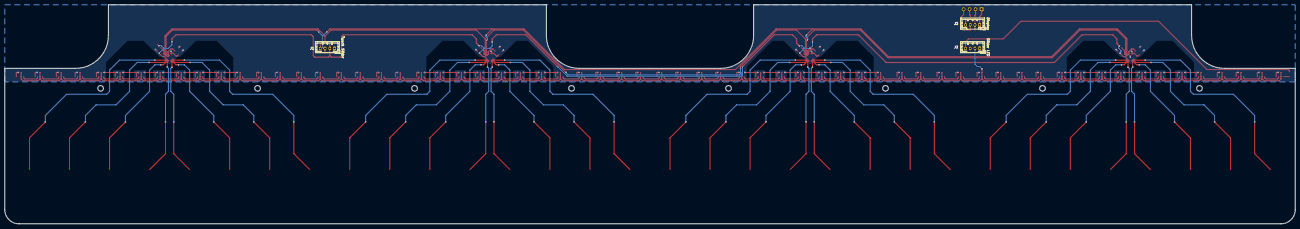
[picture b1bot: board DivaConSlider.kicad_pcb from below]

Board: 2 copper layers, 548.0 x 93.0 mm, 189 parts (3 on the bottom side), 117 nets.

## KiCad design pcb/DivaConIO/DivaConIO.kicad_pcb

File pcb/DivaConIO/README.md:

# DivaConIO - Main Board for the DivaCon2040

This board hosts a RaspberryPi Pico (or similar) microcontroller unit. It provides break out connectors for the GPIOs as well as signal shifting for WS2812 style LEDs and LED drivers for four single LEDs.

## Notes

- VBUS and VSYS are bridged as recommended in [Pico Datasheet Capter 3.5](https://datasheets.raspberrypi.com/picow/pico-w-datasheet.pdf). If you want to add external power, you can cut *JP1* to un-bridge.
- For powering active switches, like the Shinsanwa, 5V power is available on *J10*.
- If you don't need level shifting the for slider LEDs, you can omit *U2*, *C1* and *C2* and bridge *JP2* instead.

## Bill of Materials

| **Reference**           |                **Description**                |        **Digikey Part**         |                                        **Notes**                                         |
| ----------------------- | :-------------------------------------------: | :-----------------------------: | :--------------------------------------------------------------------------------------: |
| U1                      |               Raspberry Pi Pico               |        2648-SC0915CT-ND         | Other variants like the Pico W or Pico 2 should also work. Debug pins might not line up. |
| U2                      | 74LVC1T45 Dual supply translating transceiver |         1727-4560-1-ND          |                     Can be omitted if you don't need level shifting                      |
| Q1, Q2, Q3, Q4          |             BC847 NPN Transistor              |        BC847BLT3GOSCT-ND        |                                                                                          |
| C1, C2                  |          0.1µF SMD Ceramic Capacitor          |         1276-1003-1-ND          |                     Can be omitted if you don't need level shifting                      |
| R1,R2,R3,R4,R5,R6,R7,R8 |              4.7kΩ SMD Resistor               |    2019-RK73H2ATTD4701FCT-ND    |                                                                                          |
| J1,J4,J5                |       SWH201 Vertical 5 Pin Header 2mm        |            S9450-ND             |                       S9417-ND plus S9475CT-ND is the counterpart                        |
| J2,J3,J6,J7,J8,J9,10    |       SWH201 Vertical 4 Pin Header 2mm        |            S9457-ND             |                       S9406-ND plus S9475CT-ND is the counterpart                        |
| SW1                     |                Tactile Switch                 | 2223-TS02-66-60-BK-100-LCR-D-ND |                                         optional                                         |

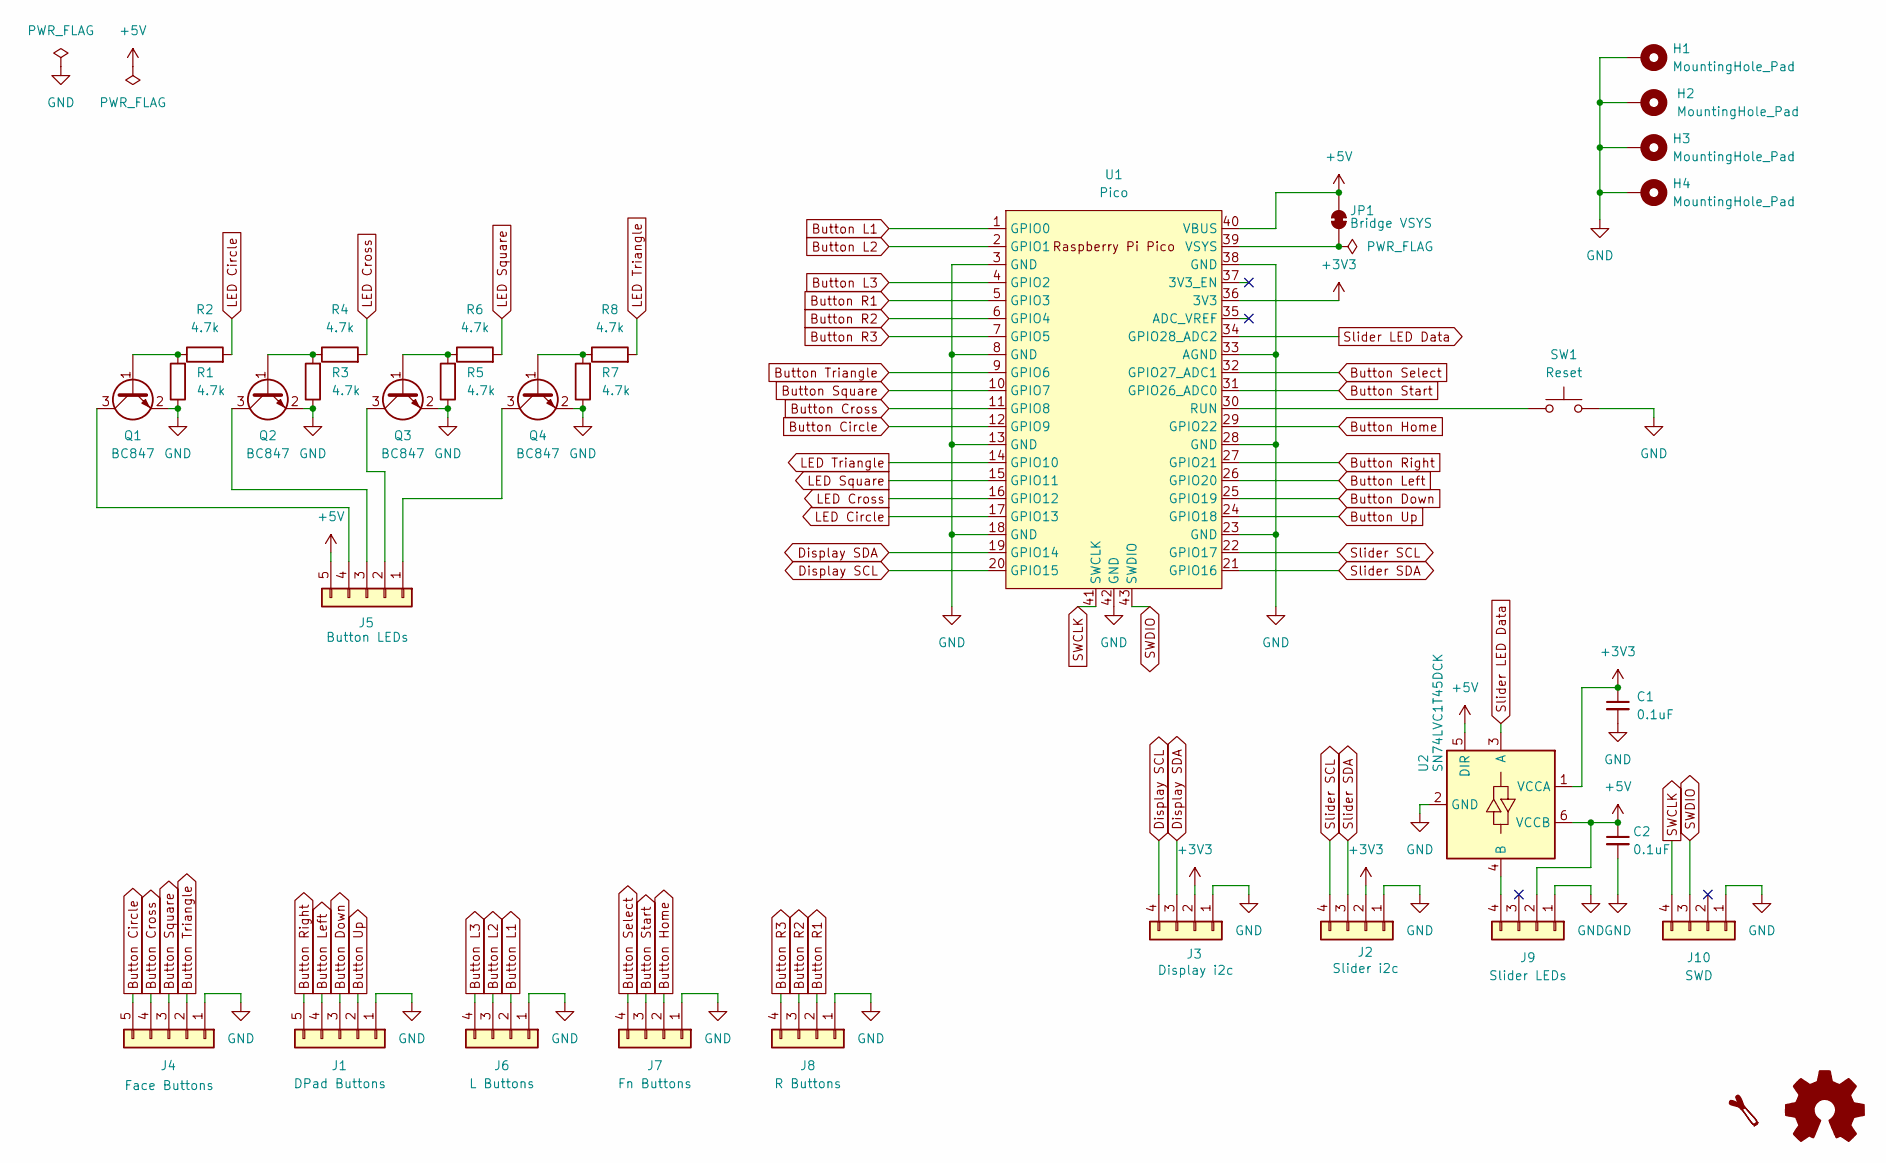
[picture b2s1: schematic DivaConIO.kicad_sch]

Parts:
C1, C2: 0.1uF; C_0805_2012Metric_Pad1.18x1.45mm_HandSolder
H1, H2, H3, H4: MountingHole_Pad; MountingHole_4.5mm_Pad_TopOnly
J1: DPad Buttons; JST_PH_B5B-PH-K_1x05_P2.00mm_Vertical
J2: Slider i2c; JST_PH_B4B-PH-K_1x04_P2.00mm_Vertical
J3: Display i2c; JST_PH_B4B-PH-K_1x04_P2.00mm_Vertical
J4: Face Buttons; JST_PH_B5B-PH-K_1x05_P2.00mm_Vertical
J5: Button LEDs; JST_PH_B5B-PH-K_1x05_P2.00mm_Vertical
J6: L Buttons; JST_PH_B4B-PH-K_1x04_P2.00mm_Vertical
J7: Fn Buttons; JST_PH_B4B-PH-K_1x04_P2.00mm_Vertical
J8: R Buttons; JST_PH_B4B-PH-K_1x04_P2.00mm_Vertical
J9: Slider LEDs; JST_PH_B4B-PH-K_1x04_P2.00mm_Vertical
J10: SWD; JST_PH_B4B-PH-K_1x04_P2.00mm_Vertical
JP1: Bridge VSYS; SolderJumper-2_P1.3mm_Bridged_RoundedPad1.0x1.5mm
Q1, Q2, Q3, Q4: BC847; SOT-23
R1, R2, R3, R4, R5, R6, R7, R8: 4.7k; R_0805_2012Metric_Pad1.20x1.40mm_HandSolder
SW1: Reset; SW_PUSH_6mm
U1: Pico; RPi_Pico_SMD_TH
U2: SN74LVC1T45DCK; SOT-363_SC-70-6_Handsoldering

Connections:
+3V3: C1.1, J2.2, J3.2, U1.36 (3V3), U2.1 (VCCA)
Button Circle: J4.5, U1.12 (GPIO9)
Button Cross: J4.4, U1.11 (GPIO8)
Button Down: J1.3, U1.25 (GPIO19)
Button Home: J7.2, U1.29 (GPIO22)
Button L1: J6.2, U1.1 (GPIO0)
Button L2: J6.3, U1.2 (GPIO1)
Button L3: J6.4, U1.4 (GPIO2)
Button Left: J1.4, U1.26 (GPIO20)
Button R1: J8.2, U1.5 (GPIO3)
Button R2: J8.3, U1.6 (GPIO4)
Button R3: J8.4, U1.7 (GPIO5)
Button Right: J1.5, U1.27 (GPIO21)
Button Select: J7.4, U1.32 (GPIO27_ADC1)
Button Square: J4.3, U1.10 (GPIO7)
Button Start: J7.3, U1.31 (GPIO26_ADC0)
Button Triangle: J4.2, U1.9 (GPIO6)
Button Up: J1.2, U1.24 (GPIO18)
Display SCL: J3.4, U1.20 (GPIO15)
Display SDA: J3.3, U1.19 (GPIO14)
GND: C1.2, C2.2, H1.1, H2.1, H3.1, H4.1, J1.1, J2.1, J3.1, J4.1, J6.1, J7.1, J8.1, J9.1, J10.1, Q1.2 (E), Q2.2 (E), Q3.2 (E), Q4.2 (E), R1.1, R3.1, R5.1, R7.1, SW1.2, U1.3 (GND), U1.8 (GND), U1.13 (GND), U1.18 (GND), U1.23 (GND), U1.28 (GND), U1.33 (AGND), U1.38 (GND), U1.42 (GND), U2.2 (GND)
LED Circle: R2.2, U1.17 (GPIO13)
LED Cross: R4.2, U1.16 (GPIO12)
LED Square: R6.2, U1.15 (GPIO11)
LED Triangle: R8.2, U1.14 (GPIO10)
unnamed: J5.1, Q4.3 (C)
unnamed: J5.2, Q3.3 (C)
unnamed: J5.3, Q2.3 (C)
unnamed: J5.4, Q1.3 (C)
unnamed 29: J9.4, U2.4 (B); also elsewhere on the board
unnamed: Q1.1 (B), R1.2, R2.1
unnamed: Q2.1 (B), R3.2, R4.1
unnamed: Q3.1 (B), R5.2, R6.1
unnamed: Q4.1 (B), R7.2, R8.1
unnamed: SW1.1, U1.30 (RUN)
SWCLK: J10.4, U1.41 (SWCLK)
SWDIO: J10.3, U1.43 (SWDIO)
Slider LED Data: U1.34 (GPIO28_ADC2), U2.3 (A); also elsewhere on the board
Slider SCL: J2.4, U1.22 (GPIO17)
Slider SDA: J2.3, U1.21 (GPIO16)

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
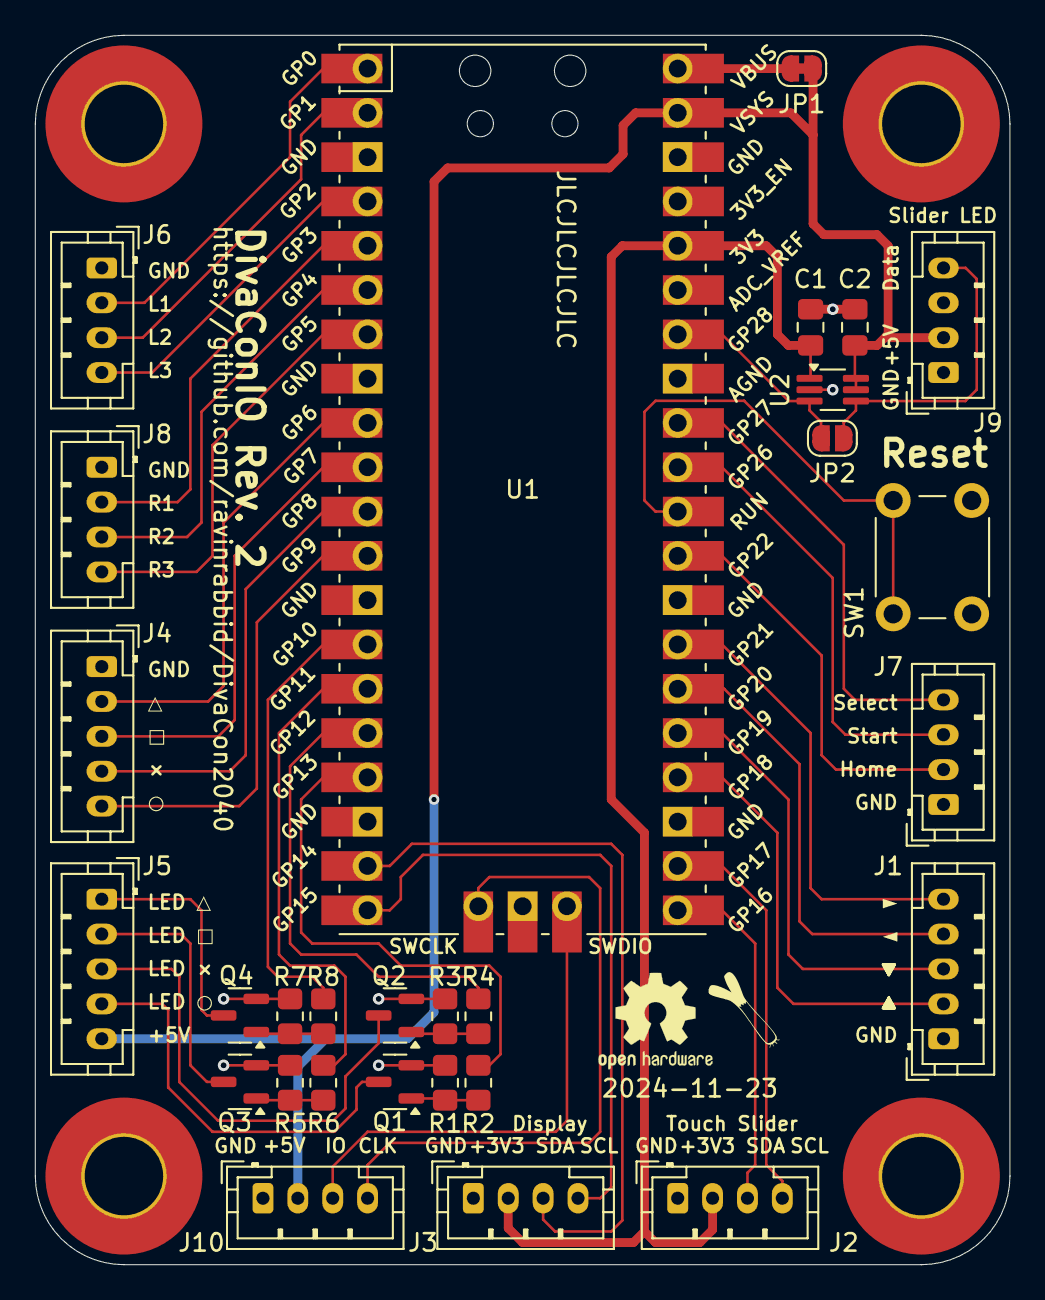
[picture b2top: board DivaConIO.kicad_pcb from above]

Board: 2 copper layers, 55.9 x 70.5 mm, 33 parts (0 on the bottom side), 42 nets.

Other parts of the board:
JP2: Bridge LED Data; SolderJumper-2_P1.3mm_Open_RoundedPad1.0x1.5mm

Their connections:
unnamed 29: JP2.2 (B); also elsewhere on the board
Slider LED Data: JP2.1 (A); also elsewhere on the board
